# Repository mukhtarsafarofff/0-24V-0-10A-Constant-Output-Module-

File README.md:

(ENG)  This 0-24V 10 Amp variable power supply circuit regulated mainly uses transistors for the power control and can be easily altered from 3 to 24 volts. The TIP3055 and BD139 transistors must be installed on appropriate heat sinks. These module can output up to 10 Amp and we can control these Amp and output Voltage.

(DEU)  Dieser variable 0-24-V-10-Ampere-Stromversorgungskreis mit Regelung verwendet hauptsächlich Transistoren für die Leistungssteuerung und kann problemlos von 3 auf 24 Volt umgestellt werden. Die TIP3055- und BD139-Transistoren müssen auf geeigneten Kühlkörpern installiert werden. Dieses Modul kann bis zu 10 Ampere ausgeben, und wir können diese Ampere sowie die Ausgangsspannung steuern.Die TIP3055- und BD139-Transistoren müssen auf geeigneten Kühlkörpern installiert werden. Dieses Modul kann bis zu 10 Ampere ausgeben, und wir können diese Ampere sowie die Ausgangsspannung steuern.

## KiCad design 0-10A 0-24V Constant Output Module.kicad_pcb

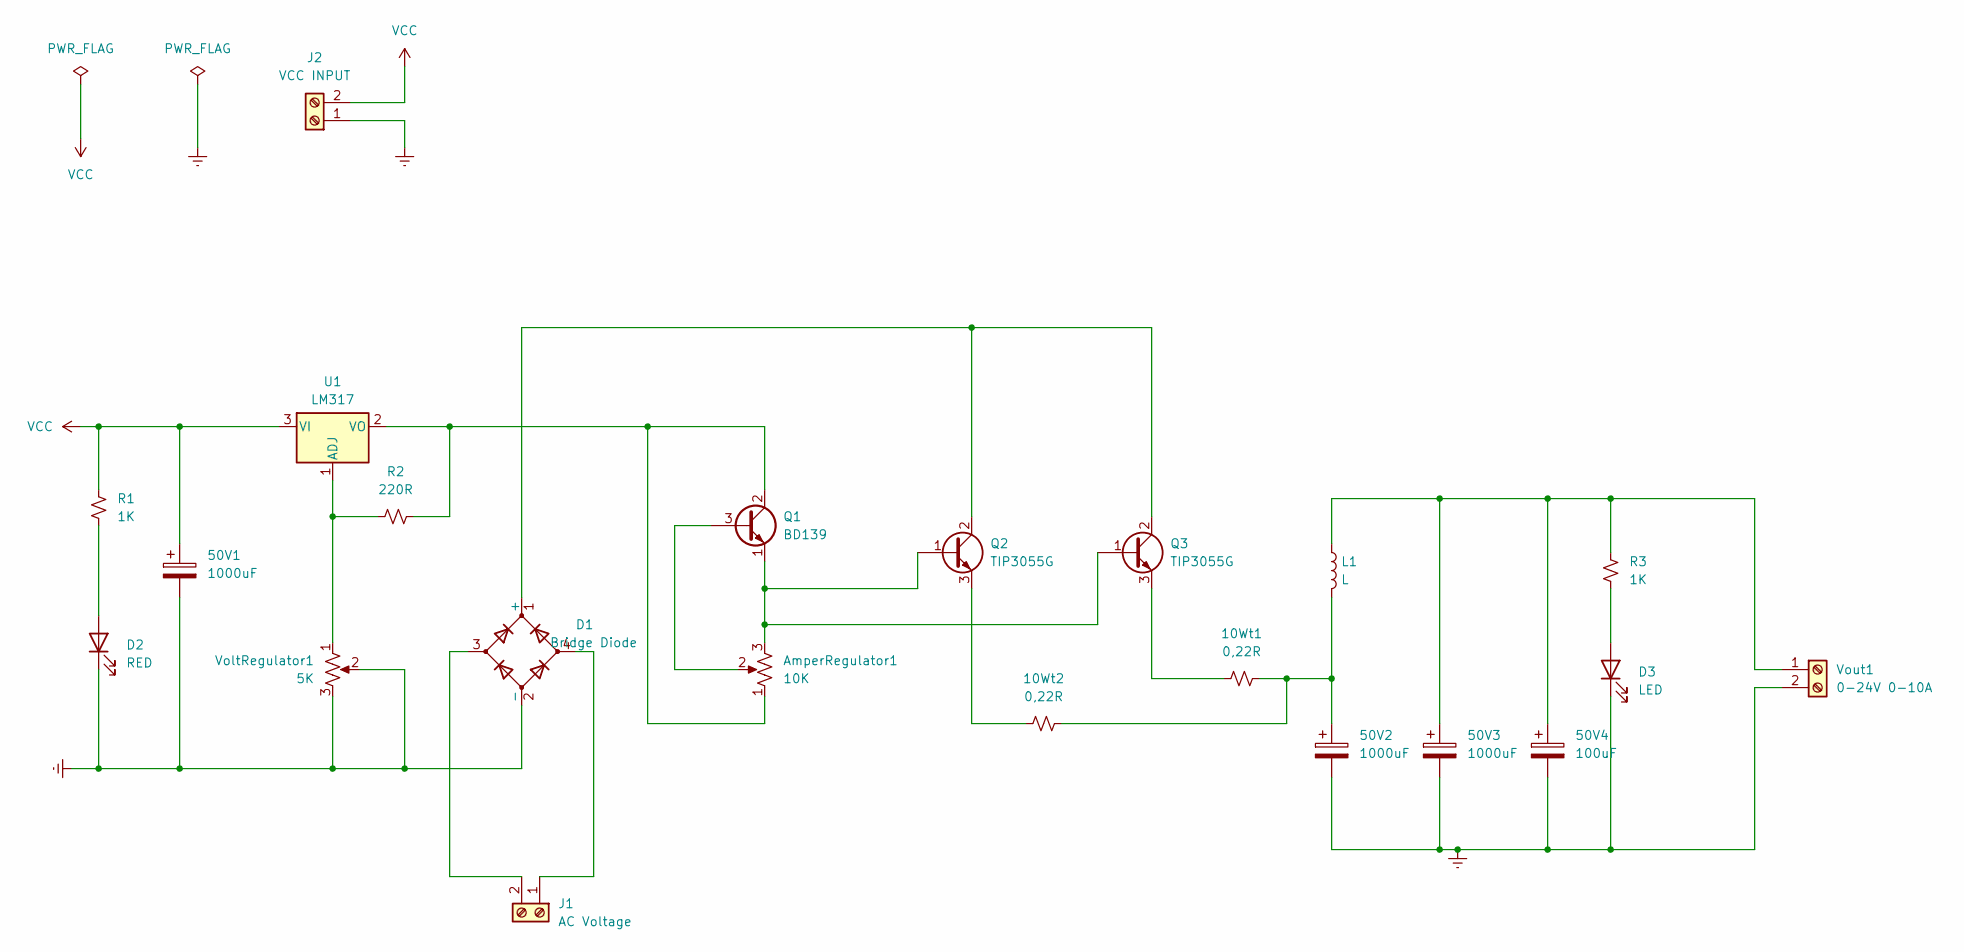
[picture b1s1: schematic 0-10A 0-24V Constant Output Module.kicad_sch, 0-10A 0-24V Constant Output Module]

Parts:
10Wt1, 10Wt2: 0,22R; R_Axial_Power_L20.0mm_W6.4mm_P30.48mm
50V1, 50V2, 50V3: 1000uF; CP_Radial_D16.0mm_P7.50mm
50V4: 100uF; CP_Radial_D10.0mm_P7.50mm
AmperRegulator1: 10K; Potentiometer_Vishay_148-149_Single_Horizontal
D1: Bridge Diode; Diode_Bridge_Vishay_GBL
D2: RED; LED_D5.0mm
D3: LED; LED_D5.0mm
J1: AC Voltage; TerminalBlock_bornier-2_P5.08mm
J2: VCC INPUT; TerminalBlock_bornier-2_P5.08mm
L1: L; L_Toroid_Horizontal_D16.8mm_P14.70mm_Vishay_TJ3_BigPads
Q1: BD139; TO-126-3_Vertical
Q2, Q3: TIP3055G; TO-247-3_Vertical
R1, R3: 1K; R_Axial_DIN0309_L9.0mm_D3.2mm_P12.70mm_Horizontal
R2: 220R; R_Axial_DIN0309_L9.0mm_D3.2mm_P12.70mm_Horizontal
U1: LM317; TO-220-3_Vertical
VoltRegulator1: 5K; Potentiometer_Vishay_148-149_Single_Horizontal
Vout1: 0-24V 0-10A; TerminalBlock_bornier-2_P5.08mm

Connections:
Earth: 50V1.2, 50V2.2, 50V3.2, 50V4.2, D1.2 (-), D2.1 (K), D3.1 (K), J2.1, VoltRegulator1.2, VoltRegulator1.3, Vout1.2
unnamed: 10Wt1.2, 10Wt2.2, 50V2.1, L1.2
unnamed: D1.1 (+), Q2.2 (C), Q3.2 (C)
unnamed: D2.2 (A), R1.2
unnamed: D3.2 (A), R3.2
unnamed: D1.4, J1.1
unnamed: D1.3, J1.2
unnamed: AmperRegulator1.2, Q1.3 (B)
unnamed: AmperRegulator1.1, Q1.2 (C), R2.2, U1.2 (VO)
unnamed: AmperRegulator1.3, Q1.1 (E), Q2.1 (B), Q3.1 (B)
unnamed: 10Wt2.1, Q2.3 (E)
unnamed: 10Wt1.1, Q3.3 (E)
unnamed: R2.1, U1.1 (ADJ), VoltRegulator1.1
unnamed: 50V3.1, 50V4.1, L1.1, R3.1, Vout1.1
VCC: 50V1.1, J2.2, R1.1, U1.3 (VI)

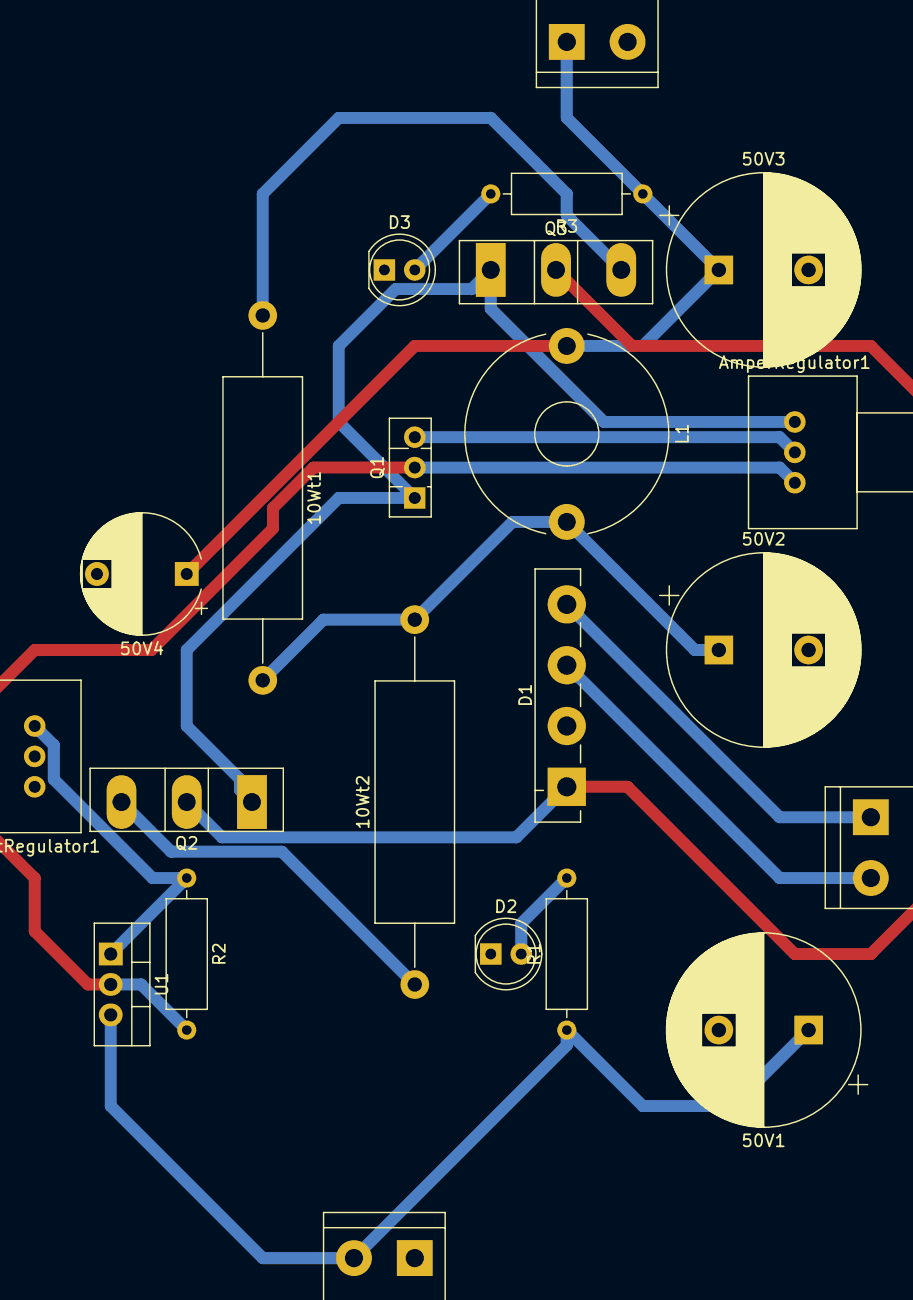
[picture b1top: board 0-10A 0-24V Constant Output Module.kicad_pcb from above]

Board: 2 copper layers, 22 parts (0 on the bottom side), 15 nets.

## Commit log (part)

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2024-04-02 0-24V 0-10A Constant Output Module is accomplished
